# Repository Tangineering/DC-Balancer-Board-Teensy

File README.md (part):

# Scale_Car_Teensy

Teensy 4.1 firmware for a scale FCHEV (Fuel-Cell Hybrid EV) platform — the **Scale Car DC
Balancer Board, Rev 20260622**.

The board is a bidirectional power-pathing balancer: ideal-diode source switches route a fuel
cell and a 2S battery onto a shared VBUS, a regen path returns braking energy to the charger,
and an MPPT module harvests into the battery. This firmware drives that hardware.

It controls:
- motor torque through a VESC (`VescUart` over UART),
- fuel-cell/battery power sharing through dual AD5443 MDAC droop outputs (SPI),
- the RT1987 ideal-diode power-path switches (6 sequenced GPIOs),
- the Silvertel **Ag105** MPPT battery charger (I2C config + `MPPT_DISABLE` GPIO),
- the BQ29200 cell OVP/balancer (`CBAL_DISABLE` GPIO),
- command/telemetry with a Raspberry Pi over UDP Ethernet,
- a safety state machine, Pi watchdog, latching fault handling, and a USB-serial test mode.

> The authoritative hardware sources are `references/Scale Car Teensy IO - IO.csv` (pin map),
> `references/Scale Car Design PCB BOM 20260622.csv` (parts), and the schematic PDF. See
> `CLAUDE.md` for the reconciliation spec and `PLAN.md` for the implementation plan. For
> hardware-in-the-loop testing (a bare Teensy against a simulated plant, no PCB needed), see
> `docs/HIL_MODE.md` (protocol/architecture) and `docs/HIL_USER_MANUAL.md` (operator manual).

## Hardware interfaces

- **UART (`Serial1`)**: VESC motor controller (`RX`=0, `TX`=1).
- **SPI**: two AD5443 MDACs (`CS_MDAC_FC`=36, `CS_MDAC_BT`=37) for FC/BT droop gains; OPA197
  output buffers run from the 5 V rail (hardware bodge).
- **I2C (`Wire`)**: Silvertel **Ag105** charger at address **0x30**.
- **Ethernet/UDP**: command in (port 5001), telemetry out (port 5000), Teensy IP 192.168.1.50.
- **Encoder interrupts**: wheel-speed estimation from `ENC_A`=14 / `ENC_B`=15 (bodged from 2/8 on
  2026-08-16; the optical sensors are hardwired to power, so there is no enable pin).
- **ADC inputs (12-bit)**: FC/BT current (INA253A1, 0.1 V/A), FC/BT/BUS/CHG/RGN voltages.
- **Digital outputs**: FC/BT boost enables, 6 RT1987 path switches, `MPPT_DISABLE`,
  `CBAL_DISABLE`, encoder enable.

### Power-path switches (RT1987 ideal-diode controllers)

| Pin | Name | Role |
|----|------|------|
| 27 | `FC_BUS_ENABLE` | FC regulator → VBUS |
| 28 | `BT_BUS_ENABLE` | BT regulator → VBUS |
| 29 | `MOT_PWR_ENABLE` | VBUS → VESC/motor (Run only) |
| 30 | `REGEN_ENABLE` | regen → charger input |
| 31 | `FC_CHARGE_ENABLE` | VBUS(FC) → charger (guarded) |
| 32 | `BT_SEQUENCE_ENABLE` | battery-pack sequencing (init LOW, then HIGH) |

All switches default LOW at boot (fail-safe; 10 kΩ EN-to-GND bodge resistors back this up).
`FC_CHARGE_ENABLE` and `REGEN_ENABLE` are **mutually exclusive** and are only ever driven
through `assertFcChargeEnable()`, which forces `BT_BUS_ENABLE` and `REGEN_ENABLE` LOW (with an
RT1987 turn-off settle delay) before opening the FC→charger path.

**VBUS bring-up — only enable a boost on a stiff source.** The hazard is *not* bus inrush: VBUS
carries only ~30–40 µF (the RT1987 ceramics); the 470 µF bulk cap is on the V-MOT/regen node behind
`MOT_PWR_ENABLE`. The real failure mode is enabling a boost on a source that can **collapse**:
switching with built-up inductor current on a sagging/recovering rail destroys the power stage. The
exact mechanism is **unconfirmed pending a scope capture** — most likely a VOUT overshoot past the
20 V SW/VOUT abs-max (the TPS61288 OVP is at 19 V, only ~0.5 V of margin, and the 3×22 µF output
caps DC-derate to ~30 µF) and/or transient reverse conduction. Either way the destructive energy
comes from the boost's own inductor/output cap, so *a supply current limit does not bound it*. On a
board-powered Teensy this also motorboats: the boost loads `VBT`, the logic rail browns out, the MCU
resets, and re-enables the boost. So in **production** (`BENCH_TEST=0`, stiff vehicle source) State 0
brings the bus up gently (switches first, then the boosts' own soft-start) and is mirrored by the
State 98 `G` command; the bus is then kept energized through Idle/Finish so a Run never re-hot-plugs
it. Under **`BENCH_TEST`** State 0 keeps the power stage **off** at boot (see State 0 below). Bench
rule: the supply must exceed the logic baseline (≥ ~0.5–1 A) or the board-powered Teensy browns out,
and the bus may be brought up (`G`) only on a stiff supply.

## Runtime flow

Main loop execution order:
1. `updateSensors()`
2. `computeDerivedSignals()`
3. `detectFaults()`
4. `checkPiWatchdog()`
5. `receiveCommands()`
6. state machine (`doState0/1/2/3/98/99`)
7. `pollAg105()` + `sendTelemetry()` at ~50 Hz

## State machine

- **State 0 (Init)**: behavior depends on the `BENCH_TEST` build flag.
  - **Production (`BENCH_TEST=0`)**: a **non-blocking phase machine** that brings VBUS up gently —
    bus switches first (`FC_BUS_ENABLE`/`BT_BUS_ENABLE`), settle, then the FC/BT boosts (their
    soft-start raises the bus; see *VBUS bring-up* above). Raises `BT_SEQUENCE_ENABLE`, inits the
    MDAC and VESC, then **gates the transition to Idle on `V_bus ≥ V_BUS_CHARGED_THRESH`**; if the
    bus never reaches it within `BUS_CHARGE_TIMEOUT_MS`, raises `FAULT_INIT_FAIL` → State 99
    (catches a dead boost, failed switch, or no source).
  - **Bench (`BENCH_TEST=1`, the default flash)**: boots **straight to Idle with the power stage
    OFF** — boosts, bus switches, and `BT_SEQUENCE` all stay LOW, and there is no `V_bus` gate. This
    prevents enabling a boost on a soft/current-limited bench supply (which browns out the
    board-powered Teensy and motorboats the boost to failure). Bring the bus up manually with the
    State 98 `G` command on a stiff supply.
  - Either way the Ag105 is **not** configured here — it is unpowered in Init; `pollAg105()`
    configures it lazily once a charger path powers it. Shared init lives in `initControlPeripherals()`.
- **State 1 (Idle)**: motor current zero, `MOT_PWR_ENABLE` LOW; the bus is left **energized**
  (boosts + bus switches stay ON). Waits for a Run command from the Pi, or `T` on USB serial to
  enter test mode (State 98).
- **State 2 (Run)**: `MOT_PWR_ENABLE` HIGH; run `chargingControl()`, `motorControl()`,
  `powerBalance()`. `chargingControl()` owns the `REGEN`/`FC_CHARGE`/`BT_BUS` switches and the
  `MPPT_DISABLE` line. The bus is already up from Init/Idle, so entering Run does not hot-plug it.
- **State 3 (Finish)**: stops the motor and closes the motor/regen/charge paths, but **leaves the
  boosts + bus switches ON** so the bus stays armed and the next Idle→Run never re-hot-plugs the
  470 µF bus. Clears the wheel-speed buffer and returns to Idle. (No cap/regen drain — the
  disabled-boost back-feed hazard doesn't apply while the boosts stay enabled.)
- **State 98 (Test)**: USB-serial hardware exerciser (see below).
- **State 99 (Error)**: **non-blocking** two-phase safe shutdown that bleeds VBUS/regen energy and
  then disables the boosts and tears the bus down — latched until power cycle (which re-runs the
  State-0 gentle bring-up).

The State 99 shutdown is a phase machine gated on `millis()` (no blocking `delay()`), so
`detectFaults()` keeps sampling through the highest-energy drain windows.

## Charger control (Silvertel Ag105)

There is **no charge-current register to program per-mA**. Control is:
- **I2C config is LAZY, not at init** (`pollAg105()`): the charger is unpowered in
  Init/Idle (no charger power path is open, so it cannot ACK I2C), so reg `0x00 = 0x01`
  (2.5 A profile) and reg `0x01 = 0x08` (2S / 8.4 V) are written the first time
  `chargerHasPower()` is true and the `AG105_SETTLE_MS` bring-up window has elapsed and
  the charger ACKs. Stored in EPROM; the flag re-arms on power loss, so writes are
  idempotent. **fw v24** adds a dynamic reg `0x02` MPPT input-voltage threshold, written
  through the same power-gated lazy path with a read-verify-write handshake and an
  EPROM-wear write-rate budget.
- **`MPPT_DISABLE` GPIO (pin 5, active-LOW)**: LOW inhibits the MPPT loop (during regen,
  so it doesn't fight the fast transient); HIGH releases it (cruise/coast harvest). The
  Ag105's MPPT mechanism is an **input-voltage-threshold regulator** (datasheet p.10),
  not perturb-and-observe — charging commences only once the input exceeds a threshold
  set by reg `0x02` (11–33 V, ~0.088 V/count; default 18 V with no MPPTS resistor
  fitted).
- **I2C polling** (`pollAg105()` at 50 Hz): reads reg `0x06` (measured charge current,
  0.011 A/count) into `I_charge`, and caches the Table-6 status byte. The Ag105 prepends its
  status byte before any read, so each 1-byte field is read as 2 bytes.
- **Readiness** (`ag105IsReady()`): GENSTAT (status bits [2:0]) == Charging (0x02) or
  Fully Charged (0x03).
- An Ag105 I2C read failure only latches State 99 in the charging-relevant states (Run/Finish);
  in Init/Idle/Test a missing or still-powering charger does not lock the system.

## Telemetry & commands

- **Commands**: 22-byte UDP packet (sync `0xBB` + XOR checksum). Fields: timestamp, counter,
  `v_setpoint`, `power_share_setpoint`, `charge_goal`, `mode_cmd`, and a reserved `droop_enable`
  byte (parsed, not yet wired).
- **Telemetry — protocol v4, 58 bytes** (`TELEMETRY_VERSION = 4`, sync `0xAA`, XOR over bytes
  1–56). Carries the measured/derived signals, droop gains, the raw Ag105 Table-6
  `charger_status` byte (offset 51), a `switch_state` bitmask of the 6 path switches, a 16-bit
  `fault_flags`, the latched `error_code`, and `error_source_state`. The Pi bridge parses fixed
  offsets and **must match this version** — see `PLAN.md` §6b for the byte-by-byte layout and the
  block comment above `sendTelemetry()`.

## Key functions

### `motorControl()` + `PI_Controller_Motor()`
Computes torque from speed error (`v_setpoint - v_actual`) and commands VESC current. The
integrator has **anti-windup**: `pi_motor_accum` is clamped to the torque equivalent of
`MOTOR_I_CMD_MAX`. Integrator state is file-scope (resettable by the unit tests).

### `powerBalance()` + `PI_Controller_Power()`
Controls the FC/BT split from measured INA253 currents; PI output (`droopRatio`) is mapped to
FC/BT droop gains and written via `setDroopMdac()` (AD5443, SPI_MODE0, MSB-first, `transfer16`).

### `chargingControl()`
Manages `MPPT_DISABLE` and the regen/FC-charge/BT-bus switches based on `charge_goal`, regen
state (`current < -0.1`), and Ag105 readiness — enforcing the FC-charge/regen mutual exclusion.

### `updateWheelSpeed()` + encoder ISRs
An **edge-period estimator** (fw v12, hardened by the fractional-pitch ledger in fw v15/v17)
measures the period between same-edge-type quadrature transitions to derive flywheel speed →
`v_actual`. It replaced the original boxcar (fixed-window sample-counting) estimator, whose
~113 ms window realized enough group delay to limit-cycle the drive loop at its own crossover.
Direction comes from the quadrature decode; a ring-invalidation event on a direction flip
holds the last valid reading (bounded by a stale timeout) rather than emitting a full-scale
zero step. State 3 resets the estimator between runs so a new run's first samples aren't
measured against stale timestamps.

## Safety features

- FC overcurrent (`I_fc > LIMIT_I_FC_MAX`), BT overcurrent (`I_batt > LIMIT_I_BT_MAX`)
- Battery UV/OV, FC UV — **UV checks are gated to Run (State 2)** so unramped rails at boot
  don't latch State 99
- Bus OV (`LIMIT_V_BUS_MAX = V_BUS_NOMINAL + 1.5 = 17.5 V` at the 16.0 V nominal, below the 19 V TPS61288 HW OVP) and Bus UV (Run only)
- Regen-node and charger-input overvoltage
- Illegal switch combination (`FC_CHARGE_ENABLE` with `BT_BUS`/`REGEN`)
- Ag105 GENSTAT error states (OC/Regulation 0x05, Thermal Shutdown 0x06, Timeout 0x07) and I2C
  comms failure
- Pi watchdog timeout (`PI_TIMEOUT_MS`, States 2/3 only)

Faults funnel through `triggerFault()`, which latches a primary `error_code` + source state and
transitions to **State 99**.

## Fault reference

When any check in `detectFaults()` trips, `triggerFault()` sets that condition's bit in the
16-bit `fault_flags`, latches the **first** cause into `error_code` (and the active state into
`error_source_state`), forces `FAULT_ERROR` (`0x8000`), and transitions to **State 99** —
latched until power cycle. Both `fault_flags` and `error_code` ride in the v4 telemetry packet,
so every value below is observable on the Pi. Read `error_code` for the root cause and
`fault_flags` for everything that tripped.

### Fault flags (`fault_flags` bitmask)

`fault_flags` is an OR of these bits — more than one can be set at once:

| Mask | Flag | Trigger | Limit | Gated to |
|------|------|---------|-------|----------|
| `0x0001` | `FAULT_OC_FC` | `I_fc` overcurrent | `LIMIT_I_FC_MAX = 3.5 A` | all |
| `0x0002` | `FAULT_UV_BATT` | `V_batt` undervoltage | `LIMIT_V_BATT_MIN = 6.2 V` | Run |
| `0x0004` | `FAULT_OV_BUS` | `V_bus` overvoltage | `LIMIT_V_BUS_MAX = 17.5 V` | all |
| `0x0008` | `FAULT_SWITCH_CONFLICT` | `FC_CHARGE_ENABLE` high while `BT_BUS`/`REGEN` high | — | all |
| `0x0010` | `FAULT_PI_TIMEOUT` | Pi watchdog expired | `PI_TIMEOUT_MS` | States 2/3 |
| `0x0020` | `FAULT_OV_BATT` | `V_batt` overvoltage | `LIMIT_V_BATT_MAX = 8.6 V` | all |
| `0x0040` | `FAULT_UV_FC` | `V_fc` undervoltage | `LIMIT_V_FC_MIN = 6.0 V` | Run |
| `0x0080` | `FAULT_OC_BT` | `I_batt` overcurrent | `LIMIT_I_BT_MAX = 6.0 A` | all |
| `0x0100` | `FAULT_UV_BUS` | `V_bus` undervoltage | `LIMIT_V_BUS_MIN = 12.0 V` | Run |
| `0x0200` | `FAULT_OV_RGN` | regen-node overvoltage | `LIMIT_V_RGN_MAX = 28.0 V` | all |
| `0x0400` | `FAULT_OV_CHG` | charger-input overvoltage | `LIMIT_V_CHG_MAX = 24.0 V` | all |
| `0x0800` | `FAULT_I2C_CHARGER` | Ag105 I2C comms failure | — | Run/Finish |
| `0x1000` | `FAULT_CHARGER_STAT` | Ag105 GENSTAT error (`0x05` OC/regulation, `0x06` thermal, `0x07` timeout) | — | charging states |
| `0x2000` | `FAULT_INIT_FAIL` | init failure: VBUS failed to reach `V_BUS_CHARGED_THRESH` within `BUS_CHARGE_TIMEOUT_MS` (also legacy Ag105 config) | `V_BUS_CHARGED_THRESH` | State 0 |
| `0x8000` | `FAULT_ERROR` | latched marker: system entered State 99 | — | set with any fault |

The UV checks marked **"Gated to Run"** are deliberately suppressed outside State 2, so unramped
rails at boot don't latch State 99 (see Safety features above).

### Error codes (`error_code` latched cause)

`error_code` is the single latched primary cause — the *first* fault to fire — and is distinct
from the multi-bit `fault_flags`. `error_source_state` records which state was active when it
latched. Values map 1:1 to `errorCodeStr()`:

| Code | Enum | String |
|------|------|--------|
| `0x00` | `ERR_NONE` | (none) |
| `0x01` | `ERR_OC_FC` | FC overcurrent |
| `0x02` | `ERR_UV_BATT` | Batt undervoltage |
| `0x03` | `ERR_OV_BUS` | Bus overvoltage |
| `0x04` | `ERR_SWITCH_CONFLICT` | Switch conflict |
| `0x05` | `ERR_PI_TIMEOUT` | Pi timeout |
| `0x06` | `ERR_OV_BATT` | Batt overvoltage |
| `0x07` | `ERR_UV_FC` | FC undervoltage |
| `0x08` | `ERR_OC_BT` | BT overcurrent |
| `0x09` | `ERR_UV_BUS` | Bus undervoltage |
| `0x0A` | `ERR_OV_RGN` | Regen overvoltage |
| `0x0B` | `ERR_OV_CHG` | Charger input OV |
| `0x0C` | `ERR_I2C_CHARGER` | Ag105 I2C fail |
| `0x0D` | `ERR_CHARGER_STAT` | Ag105 STAT fault |
| `0x0E` | `ERR_INIT_FAIL` | Init failure |

**Recovery:** State 99 is latched — a fault clears only on a power cycle. Diagnose with
`error_code` (root cause) first, then inspect the full `fault_flags` bitmask for any secondary
conditions that tripped in the same tick.

## Test mode (State 98)

State 98 is a USB-serial hardware exerciser for bench bring-up. **Enter** it by sending `T`
while in Idle (State 1); **exit** with `Q`, which returns to Idle and forces `MOT_PWR_ENABLE`
LOW. The Pi watchdog is suspended in this state, but `detectFaults()` still runs every tick — a
fault latches State 99 exactly as in normal operation. `FC_CHARGE_ENABLE` only ever moves through
`assertFcChargeEnable()`, even here.

### Serial command set

All commands are single characters over USB serial; every toggle echoes the resulting pin state
back over serial:

| Key | Action | Notes |
|-----|--------|-------|
| `F` | Toggle `FC_REG_ENABLE` (FC boost) | |
| `B` | Toggle `BT_REG_ENABLE` (BT boost) | |
| `1` | Toggle `FC_BUS_ENABLE` | **ON refused** if FC boost is ON and `V_bus` < `V_BUS_CHARGED_THRESH` (hot-plug guard — use `G`) |
| `2` | Toggle `BT_BUS_ENABLE` | same hot-plug guard as `1`; **also refused** while `FC_CHARGE_ENABLE` is HIGH (illegal combination) |
| `3` | Toggle `MOT_PWR_ENABLE` | ON allowed **only at a regulated bus** (`motPwrConnectBlocked()`); must be HIGH before `D`/`R` |
| `4` | Toggle `REGEN_ENABLE` | forces `FC_CHARGE` off via `assertFcChargeEnable(false)` before going HIGH |
| `5` | Toggle `FC_CHARGE_ENABLE` | always through the `assertFcChargeEnable()` guard |
| `6` | Toggle `BT_SEQUENCE_ENABLE` | |
| `C` | Toggle `CBAL_DISABLE` | HIGH = OVP bypassed (prints a warning) |
| `M` | Toggle `MPPT_DISABLE` | HIGH = MPPT harvesting; LOW = inhibited |
| `N` | Dynamic Ag105 MPPT reg-`0x02` threshold status/verify (fw v24) | read-verify-write handshake against the EPROM-wear write-rate budget; see `CLAUDE.md`'s 2026-09-01a addendum |
| `G` | Staged bus bring-up | `busBringupTick()` phases P0–P3: bus alone → boosts → dwell → motor node; `X` aborts (stage dark) |
| `D` | Start/stop simulated drive cycle | requires `MOT_PWR_ENABLE` HIGH and the calibrated velocity chain |
| `S` | Print status dump (all pins, ADCs, `I_charge`, faults, bench-tool state) | read-only |
| `I` | Scan the I2C bus | read-only |
| `E` | One-shot VESC firmware + telemetry read | blocks up to ~100 ms (bench-only) |
| `U` | Toggle VESC watch (~2 Hz `[VW]` line, flags fault changes) | **rebound from `W` (2026-08-10)**; auto-paused during profiles and plot mode |
| `P` | Set power-share setpoint (prompts for a value) | closed-loop: `powerBalance()` drives the MDACs live; needs current flowing |
| `O` | Set droop ratio 0.15–0.85 (prompts for a value) | open-loop direct MDAC write; no current needed — the calibration entry point |
| `A` | Set manual motor current in A (prompts) | constant VESC current, bypasses the drive controller |
| `V` | Set manual motor velocity in m/s (prompts) | refused until the velocity chain is calibrated |
| `R` | Start/stop power-share profile sweep | needs `A`/`V` set + `MOT_PWR_ENABLE` HIGH; stop parks switches |
| `T <Imax> <hold s> <rate A/s>` | Start trapezoidal current profile (one line, e.g. `T 6 5 0.5`) | direct phase-current ramp; `T` alone while running stops it; switches left as-is |
| `Y [Vmax] [b]` | Start combined drive-cycle + power-share profile (one line, both args optional, e.g. `Y 1 0.3`) | sweeps velocity **and** share together; same prerequisites as `D`; `Y` alone while running stops it |
| `W [Imax] [b]` | Start combined **current** + power-share profile (one line, both args optional, e.g. `W 6 0.0`) | same table as `Y` with the motor axis in amps; no encoder needed; `W` alone while running stops it |
| `X` | Universal stop | cancels any profile/bring-up/armed run + manual motor + live share loop |
| `L` | Toggle Serial-Plotter stream | 50 Hz `sp,act,gFC,gBT,ifc,ibt` line; suppresses status lines; `R`/`T` arm with a 5 s delay |
| `K` | Print SD-card logging status | card present, current/last file, record/drop counts; read-only |
| `H` / `?` | Print the command list | |
| `Q` | Exit → Idle (State 1) | forces `MOT_PWR_ENABLE` LOW, closes charge/regen paths, drops plot mode |

### Serial-Plotter stream (`L`)

For live plotting in the Arduino IDE (Tools → Serial Plotter). `L` toggles a condensed 50 Hz
line — `sp:…,act:…,gFC:…,gBT:…,ifc:…,ibt:…` (share setpoint, measured share, both droop gains,
both channel currents; all naturally 0–3 so the plotter's shared autoscale keeps every trace
readable). While ON, the periodic human-readable output that would break the plotter's parser is
suppressed: the `[PS]`/`[DC]`/`[TP]` 500 ms snapshots, phase banners, and the `[VW]` watch line
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
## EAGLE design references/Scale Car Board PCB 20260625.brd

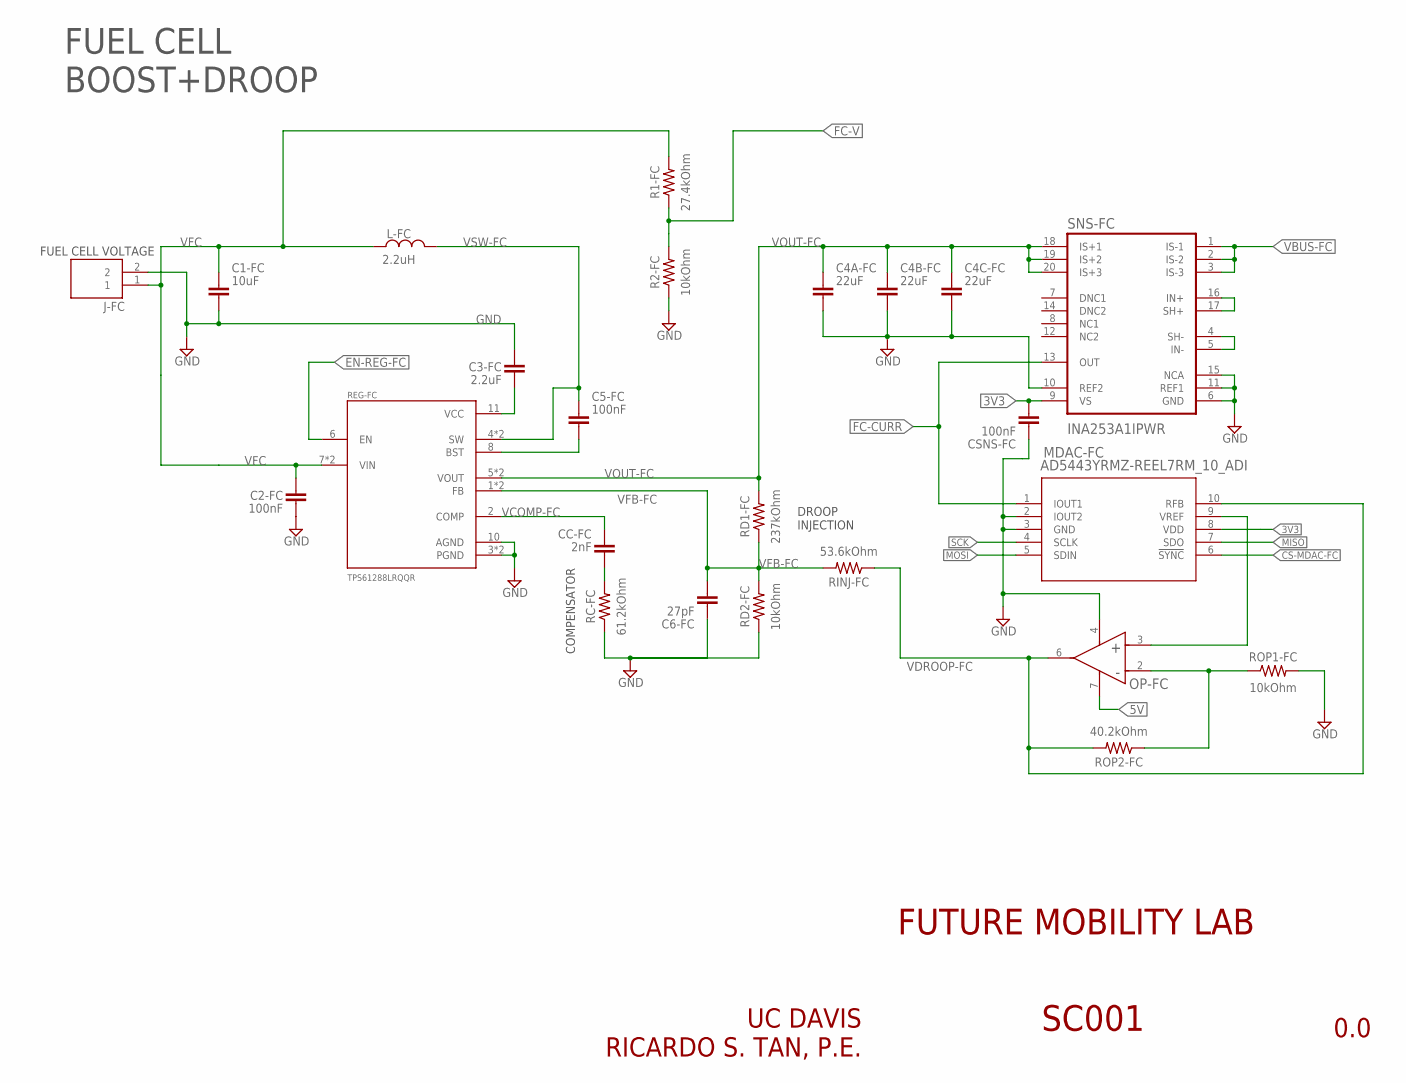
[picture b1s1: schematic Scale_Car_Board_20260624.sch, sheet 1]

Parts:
C1-FC: 10uF; CAPC2012X110
C2-FC, C5-FC: 100nF; CAPC1608X85
C3-FC: 2.2uF; CAPC2012X110
C4A-FC, C4B-FC, C4C-FC: 22uF; CAPC3225X135
C6-FC: 27pF; CAPC1608X85
CC-FC: 2nF; CAPC1608X85
CSNS-FC: 100nF; CAPC1608X85
J-FC: TB005-762-02BE; CUI_TB005-762-02BE
L-FC: 2.2uH; HCM1A1305V3-2R2-R
MDAC-FC: AD5443YRMZ-REEL7RM_10_ADI; RM_10_ADI
OP-FC: OPA197IDD0008A-IPC_A; D0008A-IPC_A
R1-FC: 27.4kOhm; RESC1608X60
R2-FC: 10kOhm; RESC1608X60
RC-FC: 61.2kOhm; RESC1608X60
RD1-FC: 237kOhm; RESC1608X60
RD2-FC: 10kOhm; RESC1608X60
REG-FC: TPS61288LRQQR; CONV_TPS61288LRQQR
RINJ-FC: 53.6kOhm; RESC1608X60
ROP1-FC: 10kOhm; RESC1608X60
ROP2-FC: 40.2kOhm; RESC1608X60
SNS-FC: INA253A1IPWR; SOP65P640X120-20N

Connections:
3V3: CSNS-FC.2, MDAC-FC.8 (VDD), SNS-FC.9 (VS); also elsewhere on the board
5V: OP-FC.7 (V+); also elsewhere on the board
CS-MDAC-FC: MDAC-FC.6 (!SYNC); also elsewhere on the board
EN-REG-FC: REG-FC.6 (EN); also elsewhere on the board
FC-CURR: MDAC-FC.1 (IOUT1), SNS-FC.13 (OUT); also elsewhere on the board
FC-V: R1-FC.1, R2-FC.2; also elsewhere on the board
GND: C1-FC.2, C2-FC.2, C3-FC.2, C4A-FC.2, C4B-FC.2, C4C-FC.2, C6-FC.1, CSNS-FC.1, J-FC.2, MDAC-FC.2 (IOUT2), MDAC-FC.3 (GND), OP-FC.4 (V-), R2-FC.1, RC-FC.1, RD2-FC.1, REG-FC.3 (PGND), REG-FC.10 (AGND), REG-FC.12 (PGND), ROP1-FC.2, SNS-FC.6 (GND), SNS-FC.10 (REF2), SNS-FC.11 (REF1), SNS-FC.15 (NCA); also elsewhere on the board
MISO: MDAC-FC.7 (SDO); also elsewhere on the board
MOSI: MDAC-FC.5 (SDIN); also elsewhere on the board
unnamed: SNS-FC.16 (IN+), SNS-FC.17 (SH+)
unnamed: CC-FC.1, RC-FC.2
unnamed: C3-FC.1, REG-FC.11 (VCC)
unnamed: C5-FC.2, REG-FC.8 (BST)
unnamed: SNS-FC.4 (SH-), SNS-FC.5 (IN-)
unnamed: MDAC-FC.9 (VREF), OP-FC.3 (+IN)
unnamed: OP-FC.2 (-IN), ROP1-FC.1, ROP2-FC.1
SCK: MDAC-FC.4 (SCLK); also elsewhere on the board
VBUS-FC: SNS-FC.1 (IS-1), SNS-FC.2 (IS-2), SNS-FC.3 (IS-3); also elsewhere on the board
VCOMP-FC: CC-FC.2, REG-FC.2 (COMP)
VDROOP-FC: MDAC-FC.10 (RFB), OP-FC.6 (OUT), RINJ-FC.1, ROP2-FC.2
VFB-FC: C6-FC.2, RD1-FC.1, RD2-FC.2, REG-FC.1 (FB), REG-FC.14 (FB), RINJ-FC.2
VFC: C1-FC.1, C2-FC.1, J-FC.1, L-FC.P$1 (1), R1-FC.2, REG-FC.7 (VIN), REG-FC.15 (VIN)
VOUT-FC: C4A-FC.1, C4B-FC.1, C4C-FC.1, RD1-FC.2, REG-FC.5 (VOUT), REG-FC.13 (VOUT), SNS-FC.18 (IS+1), SNS-FC.19 (IS+2), SNS-FC.20 (IS+3)
VSW-FC: C5-FC.1, L-FC.P$2 (2), REG-FC.4 (SW), REG-FC.9 (SW)

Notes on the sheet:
UC DAVIS RICARDO S. TAN, P.E.
FUEL CELL BOOST+DROOP
FUEL CELL VOLTAGE
DROOP INJECTION
COMPENSATOR

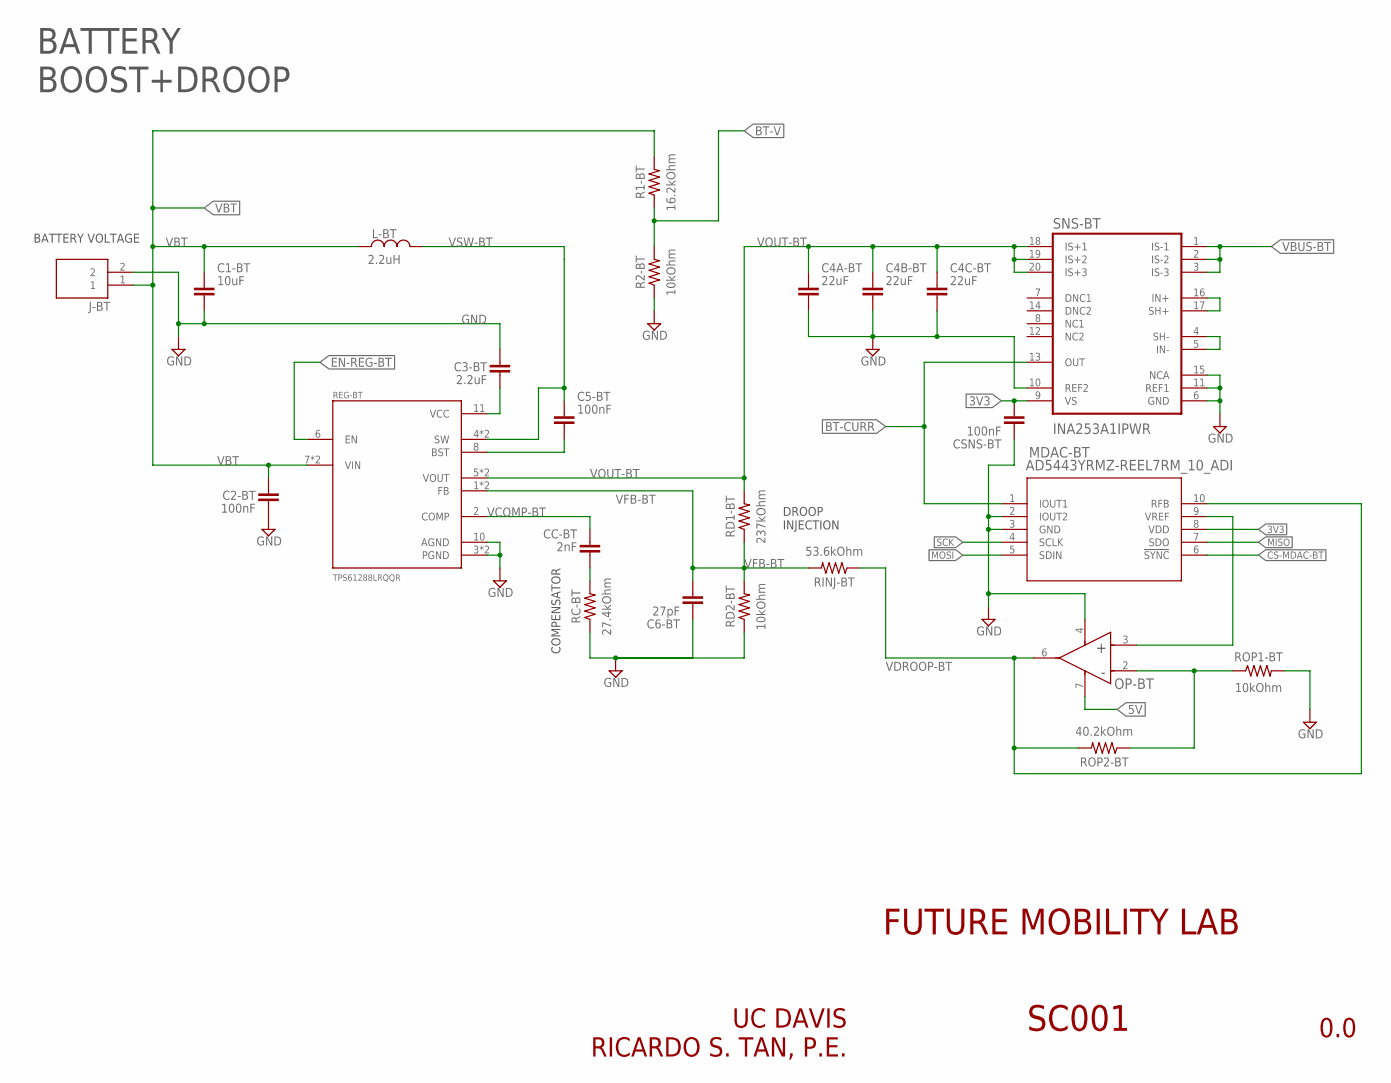
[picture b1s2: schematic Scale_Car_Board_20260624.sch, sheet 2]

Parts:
C1-BT: 10uF; CAPC2012X110
C2-BT, C5-BT: 100nF; CAPC1608X85
C3-BT: 2.2uF; CAPC2012X110
C4A-BT, C4B-BT, C4C-BT: 22uF; CAPC3225X135
C6-BT: 27pF; CAPC1608X85
CC-BT: 2nF; CAPC1608X85
CSNS-BT: 100nF; CAPC1608X85
J-BT: TB005-762-02BE; CUI_TB005-762-02BE
L-BT: 2.2uH; HCM1A1305V3-2R2-R
MDAC-BT: AD5443YRMZ-REEL7RM_10_ADI; RM_10_ADI
OP-BT: OPA197IDD0008A-IPC_A; D0008A-IPC_A
R1-BT: 16.2kOhm; RESC1608X60
R2-BT: 10kOhm; RESC1608X60
RC-BT: 27.4kOhm; RESC1608X60
RD1-BT: 237kOhm; RESC1608X60
RD2-BT: 10kOhm; RESC1608X60
REG-BT: TPS61288LRQQR; CONV_TPS61288LRQQR
RINJ-BT: 53.6kOhm; RESC1608X60
ROP1-BT: 10kOhm; RESC1608X60
ROP2-BT: 40.2kOhm; RESC1608X60
SNS-BT: INA253A1IPWR; SOP65P640X120-20N

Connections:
3V3: CSNS-BT.2, MDAC-BT.8 (VDD), SNS-BT.9 (VS); also elsewhere on the board
5V: OP-BT.7 (V+); also elsewhere on the board
BT-CURR: MDAC-BT.1 (IOUT1), SNS-BT.13 (OUT); also elsewhere on the board
BT-V: R1-BT.1, R2-BT.2; also elsewhere on the board
CS-MDAC-BT: MDAC-BT.6 (!SYNC); also elsewhere on the board
EN-REG-BT: REG-BT.6 (EN); also elsewhere on the board
GND: C1-BT.2, C2-BT.2, C3-BT.2, C4A-BT.2, C4B-BT.2, C4C-BT.2, C6-BT.1, CSNS-BT.1, J-BT.2, MDAC-BT.2 (IOUT2), MDAC-BT.3 (GND), OP-BT.4 (V-), R2-BT.1, RC-BT.1, RD2-BT.1, REG-BT.3 (PGND), REG-BT.10 (AGND), REG-BT.12 (PGND), ROP1-BT.2, SNS-BT.6 (GND), SNS-BT.10 (REF2), SNS-BT.11 (REF1), SNS-BT.15 (NCA); also elsewhere on the board
MISO: MDAC-BT.7 (SDO); also elsewhere on the board
MOSI: MDAC-BT.5 (SDIN); also elsewhere on the board
unnamed: C3-BT.1, REG-BT.11 (VCC)
unnamed: C5-BT.2, REG-BT.8 (BST)
unnamed: CC-BT.1, RC-BT.2
unnamed: SNS-BT.16 (IN+), SNS-BT.17 (SH+)
unnamed: SNS-BT.4 (SH-), SNS-BT.5 (IN-)
unnamed: MDAC-BT.9 (VREF), OP-BT.3 (+IN)
unnamed: OP-BT.2 (-IN), ROP1-BT.1, ROP2-BT.1
SCK: MDAC-BT.4 (SCLK); also elsewhere on the board
VBT: C1-BT.1, C2-BT.1, J-BT.1, L-BT.P$1 (1), R1-BT.2, REG-BT.7 (VIN), REG-BT.15 (VIN); also elsewhere on the board
VBUS-BT: SNS-BT.1 (IS-1), SNS-BT.2 (IS-2), SNS-BT.3 (IS-3); also elsewhere on the board
VCOMP-BT: CC-BT.2, REG-BT.2 (COMP)
VDROOP-BT: MDAC-BT.10 (RFB), OP-BT.6 (OUT), RINJ-BT.1, ROP2-BT.2
VFB-BT: C6-BT.2, RD1-BT.1, RD2-BT.2, REG-BT.1 (FB), REG-BT.14 (FB), RINJ-BT.2
VOUT-BT: C4A-BT.1, C4B-BT.1, C4C-BT.1, RD1-BT.2, REG-BT.5 (VOUT), REG-BT.13 (VOUT), SNS-BT.18 (IS+1), SNS-BT.19 (IS+2), SNS-BT.20 (IS+3)
VSW-BT: C5-BT.1, L-BT.P$2 (2), REG-BT.4 (SW), REG-BT.9 (SW)

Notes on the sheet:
UC DAVIS RICARDO S. TAN, P.E.
BATTERY BOOST+DROOP
BATTERY VOLTAGE
DROOP INJECTION
COMPENSATOR

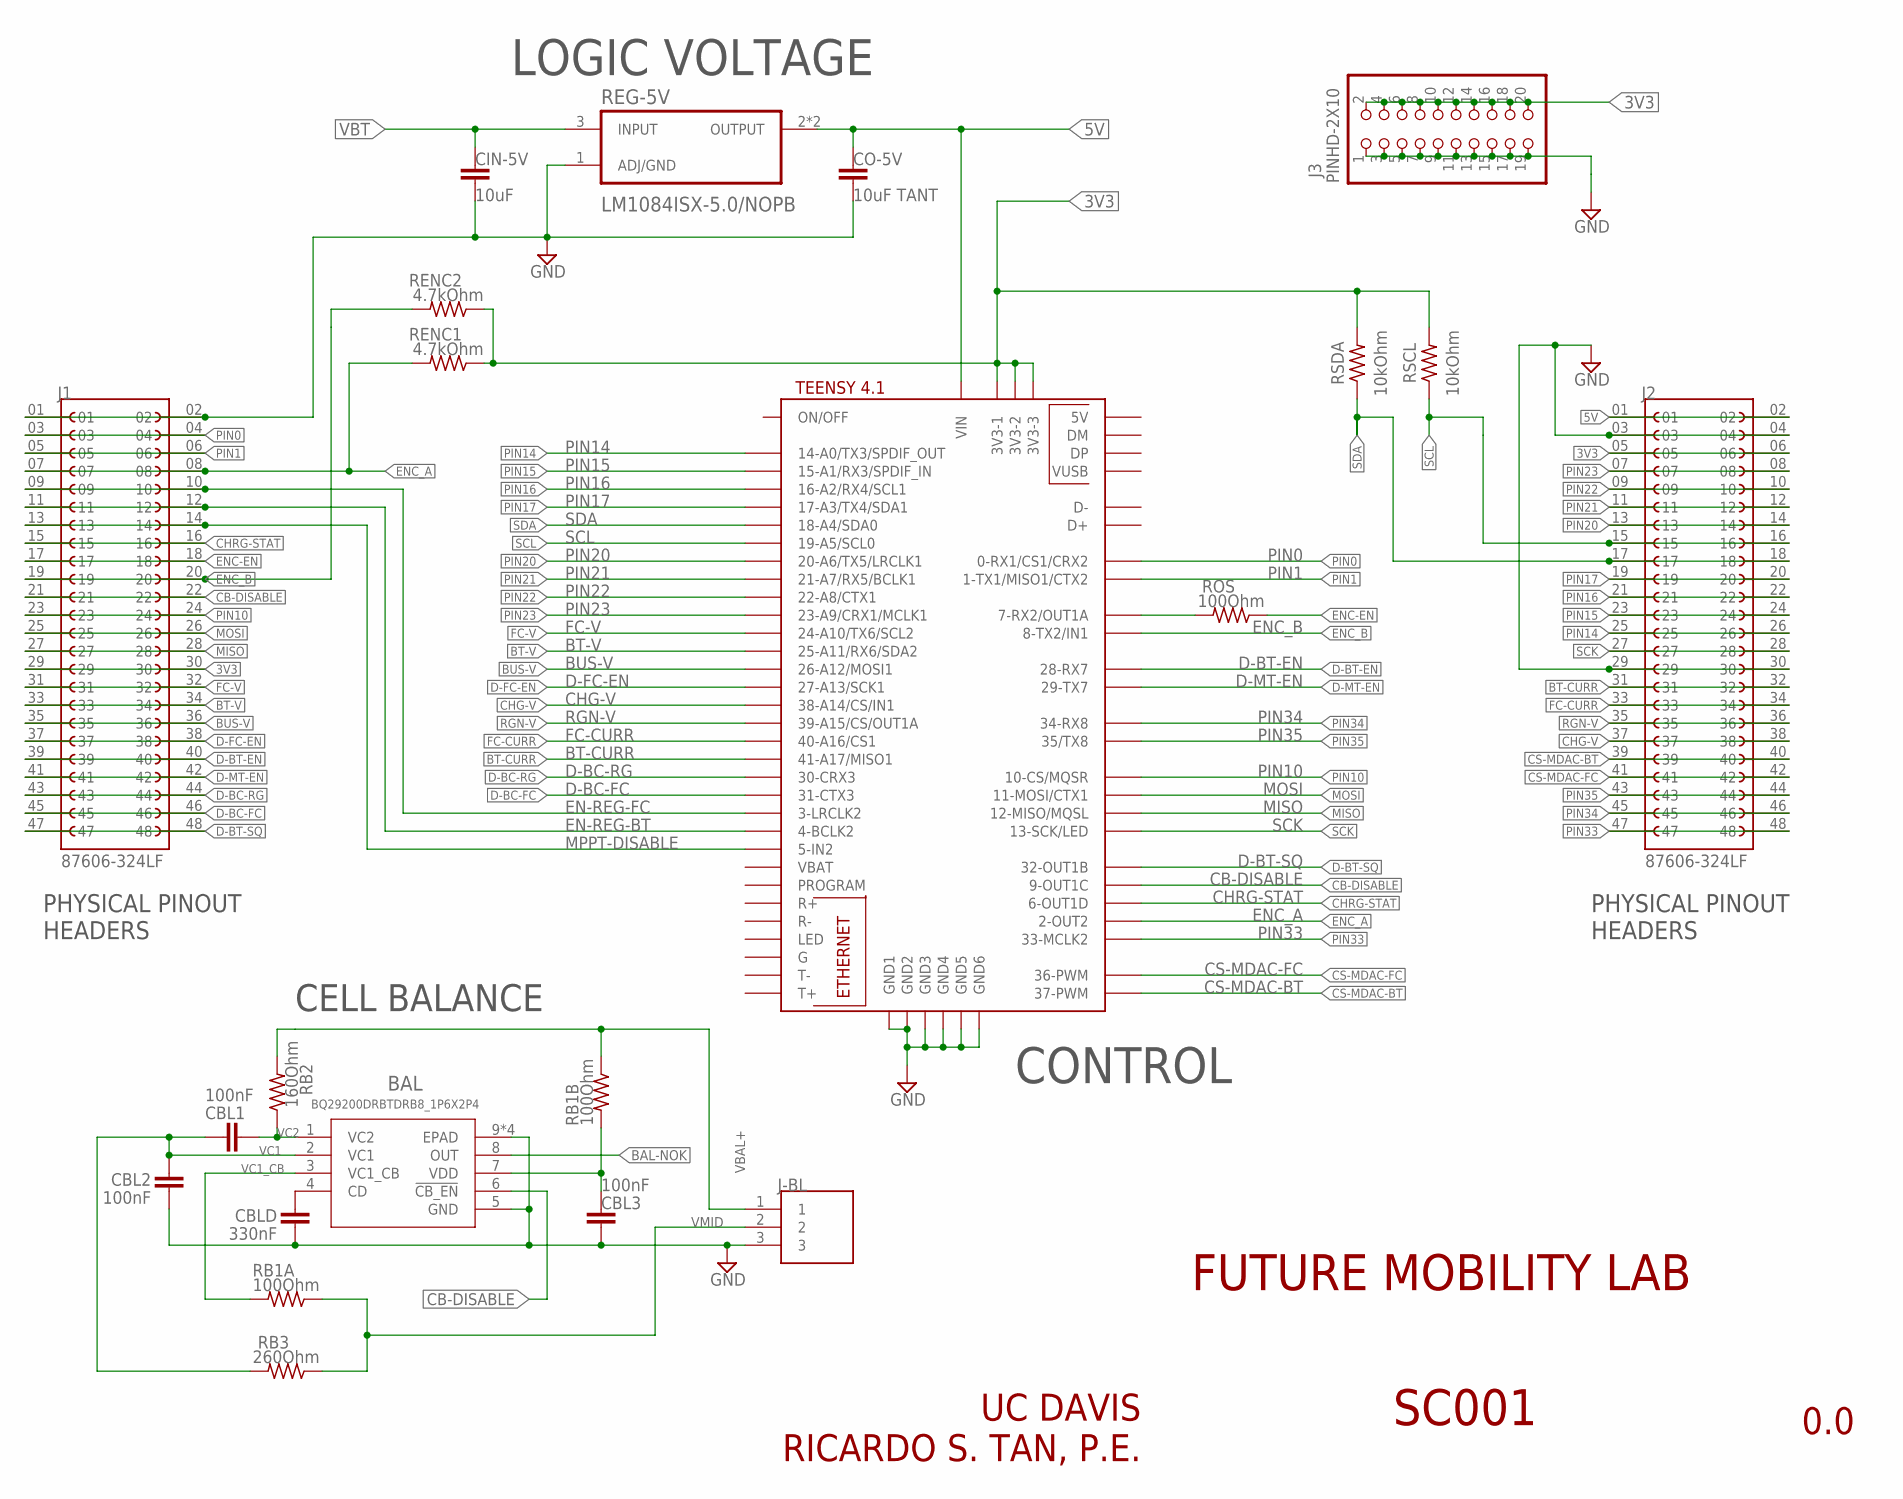
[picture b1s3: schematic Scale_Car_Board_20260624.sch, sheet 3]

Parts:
BAL: BQ29200DRBTDRB8_1P6X2P4; DRB8_1P6X2P4
CBL1, CBL2, CBL3: 100nF; CAPC1608X85
CBLD: 330nF; CAPC1608X85
CIN-5V: 10uF; CAPC2012X110
CO-5V: 10uF TANT; CAPM3528X210
J1, J2: 87606-324LF; AMPHENOL_87606-324LF
J3: PINHD-2X10; 2X10
J-BL: TB005_762_03BE; CUI_TB005_-762-03BE
RB1A, RB1B: 100Ohm; RESC1005X40
RB2: 160Ohm; RESC1005X40
RB3: 260Ohm; RESC1005X40
REG-5V: LM1084ISX-5.0/NOPB; TO254P1524X483-4N
RENC1, RENC2: 4.7kOhm; RESC1608X60
ROS: 100Ohm; RESC1608X60
RSCL: 10kOhm; RESC1608X60
RSDA: 10kOhm; RESC1608X60
U$1: TEENSY41

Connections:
3V3: J1.29, J1.30, J2.05, J2.06, J3.2, J3.4, J3.6, J3.8, J3.10, J3.12, J3.14, J3.16, J3.18, J3.20, RENC1.1, RENC2.1, RSCL.2, RSDA.2, U$1.3V3-1, U$1.3V3-2, U$1.3V3-3; also elsewhere on the board
5V: CO-5V.1, J2.01, J2.02, REG-5V.2 (OUTPUT), REG-5V.4 (OUTPUT), U$1.VIN; also elsewhere on the board
BAL-NOK: BAL.8 (OUT)
BT-CURR: J2.31, J2.32, U$1.41-A17/MISO1; also elsewhere on the board
BT-V: J1.33, J1.34, U$1.25-A11/RX6/SDA2; also elsewhere on the board
BUS-V: J1.35, J1.36, U$1.26-A12/MOSI1; also elsewhere on the board
CB-DISABLE: BAL.6 (!CB_EN), J1.21, J1.22, U$1.9-OUT1C
CHG-V: J2.37, J2.38, U$1.38-A14/CS/IN1; also elsewhere on the board
CHRG-STAT: J1.15, J1.16, U$1.6-OUT1D; also elsewhere on the board
CS-MDAC-BT: J2.39, J2.40, U$1.37-PWM; also elsewhere on the board
CS-MDAC-FC: J2.41, J2.42, U$1.36-PWM; also elsewhere on the board
D-BC-FC: J1.45, J1.46, U$1.31-CTX3; also elsewhere on the board
D-BC-RG: J1.43, J1.44, U$1.30-CRX3; also elsewhere on the board
D-BT-EN: J1.39, J1.40, U$1.28-RX7; also elsewhere on the board
D-BT-SQ: J1.47, J1.48, U$1.32-OUT1B; also elsewhere on the board
D-FC-EN: J1.37, J1.38, U$1.27-A13/SCK1; also elsewhere on the board
D-MT-EN: J1.41, J1.42, U$1.29-TX7; also elsewhere on the board
EN-REG-BT: J1.11, J1.12, U$1.4-BCLK2; also elsewhere on the board
EN-REG-FC: J1.09, J1.10, U$1.3-LRCLK2; also elsewhere on the board
ENC-EN: J1.17, J1.18, ROS.1
ENC_A: J1.07, J1.08, RENC1.2, U$1.2-OUT2
ENC_B: J1.19, J1.20, RENC2.2, U$1.8-TX2/IN1
FC-CURR: J2.33, J2.34, U$1.40-A16/CS1; also elsewhere on the board
FC-V: J1.31, J1.32, U$1.24-A10/TX6/SCL2; also elsewhere on the board
GND: BAL.5 (GND), BAL.9 (EPAD), BAL.V (EPAD), BAL.V_2 (EPAD), BAL.V_4 (EPAD), CBL2.2, CBL3.2, CBLD.2, CIN-5V.2, CO-5V.2, J1.01, J1.02, J2.03, J2.04, J2.29, J2.30, J3.1, J3.3, J3.5, J3.7, J3.9, J3.11, J3.13, J3.15, J3.17, J3.19, J-BL.3, REG-5V.1 (ADJ/GND), U$1.GND1, U$1.GND2, U$1.GND3, U$1.GND4, U$1.GND5, U$1.GND6; also elsewhere on the board
MISO: J1.27, J1.28, U$1.12-MISO/MQSL; also elsewhere on the board
MOSI: J1.25, J1.26, U$1.11-MOSI/CTX1; also elsewhere on the board
MPPT-DISABLE: J1.13, J1.14, U$1.5-IN2; also elsewhere on the board
unnamed: ROS.2, U$1.7-RX2/OUT1A
unnamed: BAL.4 (CD), CBLD.1
unnamed: BAL.7 (VDD), CBL3.1, RB1B.2
PIN0: J1.03, J1.04, U$1.0-RX1/CS1/CRX2
PIN1: J1.05, J1.06, U$1.1-TX1/MISO1/CTX2
PIN10: J1.23, J1.24, U$1.10-CS\MQSR (10-CS/MQSR)
PIN14: J2.25, J2.26, U$1.14-A0/TX3/SPDIF_OUT
PIN15: J2.23, J2.24, U$1.15-A1/RX3/SPDIF_IN
PIN16: J2.21, J2.22, U$1.16-A2/RX4/SCL1
PIN17: J2.19, J2.20, U$1.17-A3/TX4/SDA1
PIN20: J2.13, J2.14, U$1.20-A6/TX5/LRCLK1
PIN21: J2.11, J2.12, U$1.21-A7/RX5/BCLK1
PIN22: J2.09, J2.10, U$1.22-A8/CTX1
PIN23: J2.07, J2.08, U$1.23-A9/CRX1/MCLK1
PIN33: J2.47, J2.48, U$1.33-MCLK2
PIN34: J2.45, J2.46, U$1.34-RX8
PIN35: J2.43, J2.44, U$1.35-TX8 (35/TX8)
RGN-V: J2.35, J2.36, U$1.39-A15/CS/OUT1A; also elsewhere on the board
SCK: J2.27, J2.28, U$1.13-SCK/LED; also elsewhere on the board
SCL: J2.15, J2.16, RSCL.1, U$1.19-A5/SCL0; also elsewhere on the board
SDA: J2.17, J2.18, RSDA.1, U$1.18-A4/SDA0; also elsewhere on the board
VBAL+: J-BL.1, RB1B.1, RB2.2
VBT: CIN-5V.1, REG-5V.3 (INPUT); also elsewhere on the board
VC1: BAL.2 (VC1), CBL1.1, CBL2.1, RB3.2
VC1_CB: BAL.3 (VC1_CB), RB1A.2
VC2: BAL.1 (VC2), CBL1.2, RB2.1
VMID: J-BL.2, RB1A.1, RB3.1

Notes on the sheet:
UC DAVIS RICARDO S. TAN, P.E.
CONTROL
PHYSICAL PINOUT HEADERS
LOGIC VOLTAGE
CELL BALANCE

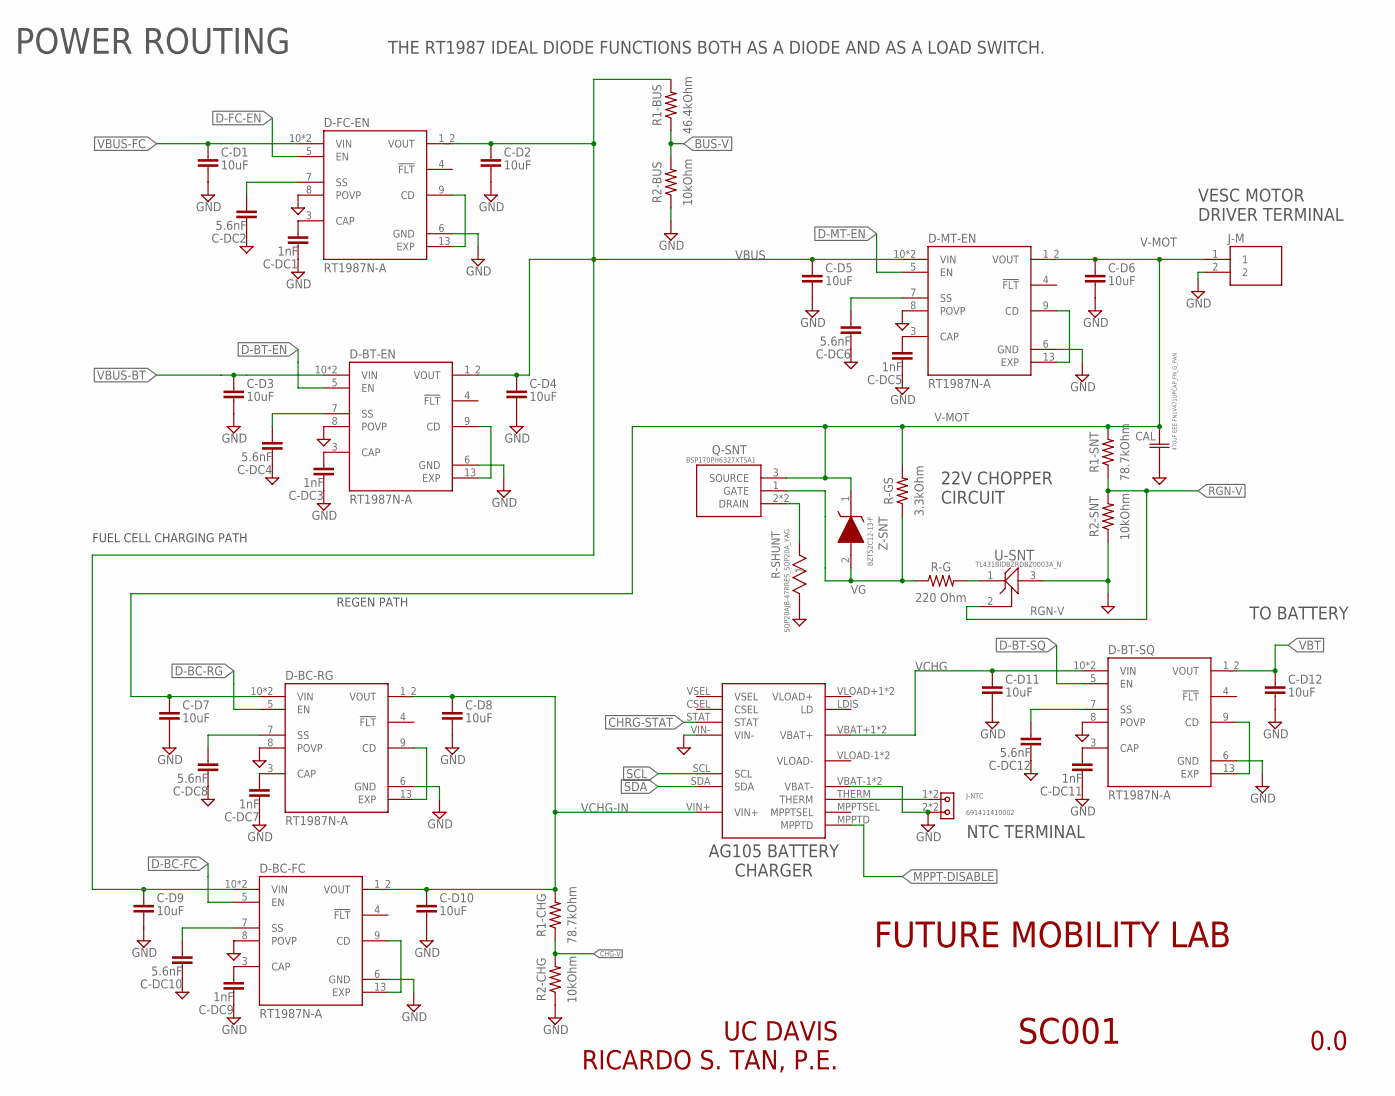
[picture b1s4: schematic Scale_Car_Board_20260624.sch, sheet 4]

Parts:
C-D1, C-D2, C-D3, C-D4, C-D5, C-D8, C-D10, C-D11, C-D12: 10uF; CAPC2012X110
C-D6, C-D7, C-D9: 10uF; CAPC3216X135
C-DC1, C-DC3, C-DC5, C-DC7, C-DC9, C-DC11: 1nF; CAPC1005X60
C-DC2, C-DC4, C-DC6, C-DC8, C-DC10, C-DC12: 5.6nF; CAPC1005X60
CAL: 470uF EEE-FN1V471UPCAP_FN_G_PAN; CAP_FN_G_PAN
CHG: AG105
D-BC-FC: RT1987N-A; IC_RT1987N-A
D-BC-RG: RT1987N-A; IC_RT1987N-A
D-BT-EN: RT1987N-A; IC_RT1987N-A
D-BT-SQ: RT1987N-A; IC_RT1987N-A
D-FC-EN: RT1987N-A; IC_RT1987N-A
D-MT-EN: RT1987N-A; IC_RT1987N-A
J-M: TB005-762-02BE; CUI_TB005-762-02BE
J-NTC: 691411410002
Q-SNT: BSP170PH6327XTSA1; SOT230P700X170-4N
R1-BUS: 46.4kOhm; RESC1608X60
R1-CHG, R1-SNT: 78.7kOhm; RESC1005X40
R2-BUS, R2-CHG, R2-SNT: 10kOhm; RESC1608X60
R-G: 220 Ohm; RESC1005X40
R-GS: 3.3kOhm; RESC1608X60
R-SHUNT: SQP20AJB-47RRES_SQP20A_YAG; RES_SQP20A_YAG
U-SNT: TL431BIDBZRDBZ0003A_N; DBZ0003A_N
Z-SNT: BZT52C12-13-F; SOD3716X145N

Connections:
BUS-V: R1-BUS.1, R2-BUS.2; also elsewhere on the board
CHG-V: R1-CHG.1, R2-CHG.2; also elsewhere on the board
CHRG-STAT: CHG.STAT; also elsewhere on the board
D-BC-FC: D-BC-FC.5 (EN); also elsewhere on the board
D-BC-RG: D-BC-RG.5 (EN); also elsewhere on the board
D-BT-EN: D-BT-EN.5 (EN); also elsewhere on the board
D-BT-SQ: D-BT-SQ.5 (EN); also elsewhere on the board
D-FC-EN: D-FC-EN.5 (EN); also elsewhere on the board
D-MT-EN: D-MT-EN.5 (EN); also elsewhere on the board
GND: C-D1.2, C-D2.2, C-D3.2, C-D4.2, C-D5.2, C-D6.2, C-D7.2, C-D8.2, C-D9.2, C-D10.2, C-D11.2, C-D12.2, C-DC1.1, C-DC2.1, C-DC3.1, C-DC4.1, C-DC5.1, C-DC6.1, C-DC7.1, C-DC8.1, C-DC9.1, C-DC10.1, C-DC11.1, C-DC12.1, CAL.2, CHG.VBAT-1 (VBAT-), CHG.VBAT-2 (VBAT-), CHG.VIN-, D-BC-FC.6 (GND), D-BC-FC.8 (POVP), D-BC-RG.6 (GND), D-BC-RG.8 (POVP), D-BT-EN.6 (GND), D-BT-EN.8 (POVP), D-BT-SQ.6 (GND), D-BT-SQ.8 (POVP), D-FC-EN.6 (GND), D-FC-EN.8 (POVP), D-MT-EN.6 (GND), D-MT-EN.8 (POVP), J-M.2, J-NTC.2, J-NTC.A2 (2), R2-BUS.1, R2-CHG.1, R2-SNT.1, R-SHUNT.2, U-SNT.3 (ANODE); also elsewhere on the board
MPPT-DISABLE: CHG.MPPTD; also elsewhere on the board
unnamed: C-DC1.2, D-FC-EN.3 (CAP)
unnamed: C-DC3.2, D-BT-EN.3 (CAP)
unnamed: D-FC-EN.9 (CD), D-FC-EN.13 (EXP)
unnamed: C-DC2.2, D-FC-EN.7 (SS)
unnamed: D-BT-EN.9 (CD), D-BT-EN.13 (EXP)
unnamed: C-DC4.2, D-BT-EN.7 (SS)
unnamed: C-DC5.2, D-MT-EN.3 (CAP)
unnamed: C-DC7.2, D-BC-RG.3 (CAP)
unnamed: D-MT-EN.9 (CD), D-MT-EN.13 (EXP)
unnamed: C-DC6.2, D-MT-EN.7 (SS)
unnamed: D-BC-RG.9 (CD), D-BC-RG.13 (EXP)
unnamed: C-DC8.2, D-BC-RG.7 (SS)
unnamed: C-DC9.2, D-BC-FC.3 (CAP)
unnamed: D-BC-FC.9 (CD), D-BC-FC.13 (EXP)
unnamed: C-DC10.2, D-BC-FC.7 (SS)
unnamed: C-DC11.2, D-BT-SQ.3 (CAP)
unnamed: D-BT-SQ.9 (CD), D-BT-SQ.13 (EXP)
unnamed: C-DC12.2, D-BT-SQ.7 (SS)
unnamed: CHG.THERM, J-NTC.1, J-NTC.A1 (1)
unnamed: R-G.2, U-SNT.1 (CATHODE)
unnamed: Q-SNT.2 (DRAIN), Q-SNT.4 (DRAIN), R-SHUNT.1
RGN-V: R1-SNT.1, R2-SNT.2, U-SNT.2 (REF); also elsewhere on the board
SCL: CHG.SCL; also elsewhere on the board
SDA: CHG.SDA; also elsewhere on the board
V-MOT: C-D6.1, C-D7.1, CAL.1, D-BC-RG.10 (VIN), D-BC-RG.11_12 (VIN), D-MT-EN.1_2 (VOUT), J-M.1, Q-SNT.3 (SOURCE), R1-SNT.2, R-GS.2, Z-SNT.1 (K)
VBT: C-D12.1, D-BT-SQ.1_2 (VOUT); also elsewhere on the board
VBUS: C-D2.1, C-D4.1, C-D5.1, C-D9.1, D-BC-FC.10 (VIN), D-BC-FC.11_12 (VIN), D-BT-EN.1_2 (VOUT), D-FC-EN.1_2 (VOUT), D-MT-EN.10 (VIN), D-MT-EN.11_12 (VIN), R1-BUS.2
VBUS-BT: C-D3.1, D-BT-EN.10 (VIN), D-BT-EN.11_12 (VIN); also elsewhere on the board
VBUS-FC: C-D1.1, D-FC-EN.10 (VIN), D-FC-EN.11_12 (VIN); also elsewhere on the board
VCHG: C-D11.1, CHG.VBAT+1 (VBAT+), CHG.VBAT+2 (VBAT+), D-BT-SQ.10 (VIN), D-BT-SQ.11_12 (VIN)
VCHG-IN: C-D8.1, C-D10.1, CHG.VIN+, D-BC-FC.1_2 (VOUT), D-BC-RG.1_2 (VOUT), R1-CHG.2
VG: Q-SNT.1 (GATE), R-G.1, R-GS.1, Z-SNT.2 (A)

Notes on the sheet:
UC DAVIS RICARDO S. TAN, P.E.
POWER ROUTING
VESC MOTOR DRIVER TERMINAL
REGEN PATH
FUEL CELL CHARGING PATH
NTC TERMINAL
AG105 BATTERY CHARGER
THE RT1987 IDEAL DIODE FUNCTIONS BOTH AS A DIODE AND AS A LOAD SWITCH.
22V CHOPPER CIRCUIT
TO BATTERY

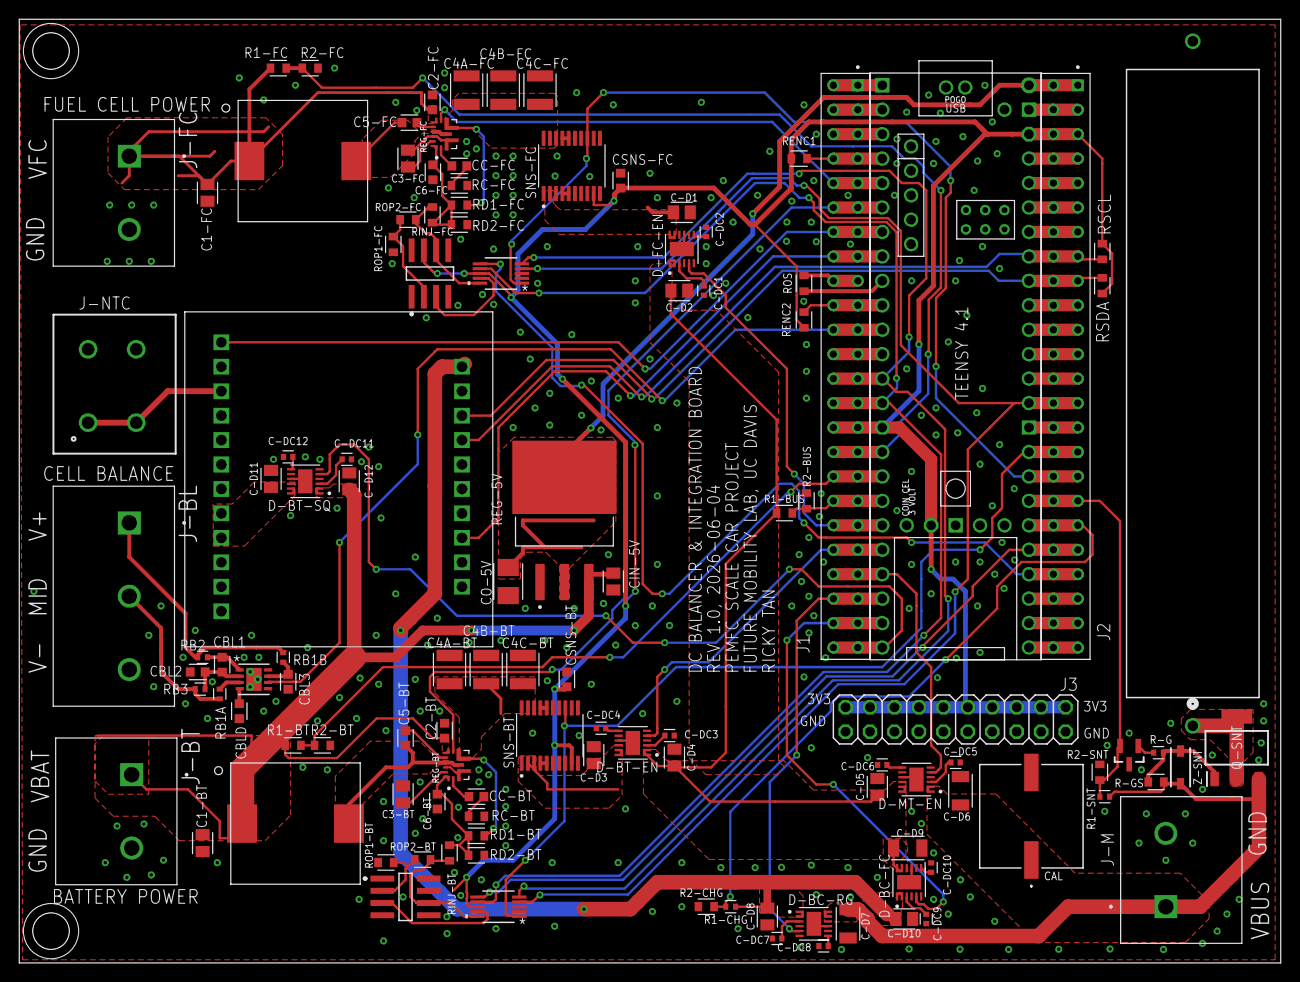
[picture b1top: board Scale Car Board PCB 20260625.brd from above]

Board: 2 copper layers, 131.1 x 98.0 mm, 116 parts (0 on the bottom side), 107 nets.

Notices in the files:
parts and their libraries:
COPYRIGHT: Copyright (C) 2026 Ultra Librarian. All rights reserved.
